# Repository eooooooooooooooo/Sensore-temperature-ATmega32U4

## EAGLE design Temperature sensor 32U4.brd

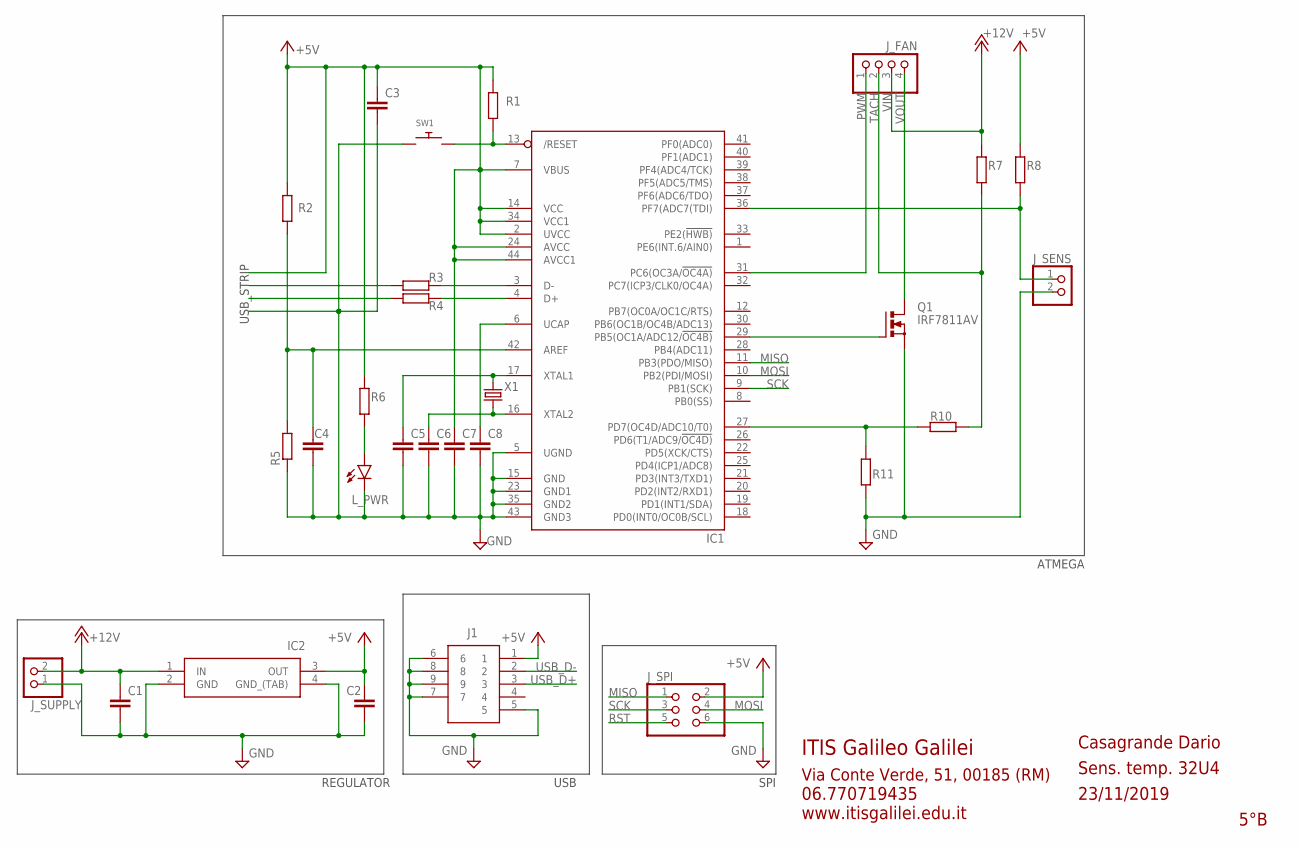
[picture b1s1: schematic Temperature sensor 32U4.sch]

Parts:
C1: 470n; C1206
C2: 47u; C1206
C3, C4, C8: 1u; C1206
C5, C6: 22p; C1206
C7: 100n; C1206
IC1: ATMEGA32U4-AU; TQFP44
IC2: LM2940CS-5.0_NOPB; TO254P1435X464-4N
J1: 10104111-0001LF; 101041110001LF
J_FAN: PINHD-1X4; 1X04
J_SENS: PINHD-1X2; 1X02
J_SPI: PINHD-2X3; 2X03
J_SUPPLY: PINHD-1X2; 1X02
L_PWR: LEDCHIPLED_1206; CHIPLED_1206
Q1: IRF7811AV; SO-08
R1, R7, R8, R10: 10k; R1206
R2: 1,8k; R1206
R3, R4: 10; R1206
R5: 8,2k; R1206
R6: 270; R1206
R11: 14k; R1206
SW1: SWITCH_PUSHBUTTONSOFTTOUCHSMD_SJ; PUSHBUTTON_SMD_SJ
X1: 16MHz; HC49/S

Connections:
+5V: C2.1, C3.1, C7.1, IC1.2 (UVCC), IC1.7 (VBUS), IC1.14 (VCC), IC1.24 (AVCC), IC1.34 (VCC1), IC1.44 (AVCC1), IC2.3 (OUT), J1.1, J_SPI.2, R1.2, R2.2, R6.1, R8.1
+12V: C1.1, IC2.1 (IN), J_SUPPLY.2
AREF: C4.1, IC1.42 (AREF), R2.1, R5.2
D+: IC1.4 (D+), R4.1
D-: IC1.3 (D-), R3.1
GND: C1.2, C2.2, C3.2, C4.2, C5.2, C6.2, C7.2, C8.2, IC1.5 (UGND), IC1.15 (GND), IC1.23 (GND1), IC1.35 (GND2), IC1.43 (GND3), IC2.2 (GND), IC2.4 (GND_(TAB)), J1.5, J1.6, J1.7, J1.8, J1.9, J_SENS.2, J_SPI.6, J_SUPPLY.1, L_PWR.C, Q1.1 (S), Q1.2 (S), Q1.3 (S), R5.1, R11.2, SW1.P$1
MISO: IC1.11 (PB3(PDO/MISO)), J_SPI.1
MOSI: IC1.10 (PB2(PDI/MOSI)), J_SPI.4
unnamed: L_PWR.A, R6.2
unnamed: IC1.29 (PB5(OC1A/ADC12/!OC4B)), Q1.4 (G)
PWM: IC1.31 (PC6(OC3A/!OC4A)), J_FAN.1
RST: IC1.13 (/RESET), J_SPI.5, R1.1, SW1.P$2
SCK: IC1.9 (PB1(SCK)), J_SPI.3
SENS: IC1.36 (PF7(ADC7(TDI)), J_SENS.1, R8.2
TACH: J_FAN.2, R7.2, R10.1
TACH_IN: IC1.27 (PD7(OC4D/ADC10/T0)), R10.2, R11.1
UCAP: C8.1, IC1.6 (UCAP)
USB_D+: J1.3, R4.2
USB_D-: J1.2, R3.2
VIN: J_FAN.3, R7.1
VOUT: J_FAN.4, Q1.5 (D), Q1.6 (D), Q1.7 (D), Q1.8 (D)
XTAL1: C5.1, IC1.17 (XTAL1), X1.2
XTAL2: C6.1, IC1.16 (XTAL2), X1.1

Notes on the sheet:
5°B
Casagrande Dario
Sens. temp. 32U4
23/11/2019
ITIS Galileo Galilei
Via Conte Verde, 51, 00185 (RM)
www.itisgalilei.edu.it
06.770719435
USB
SPI
REGULATOR
ATMEGA
USB_STRIP

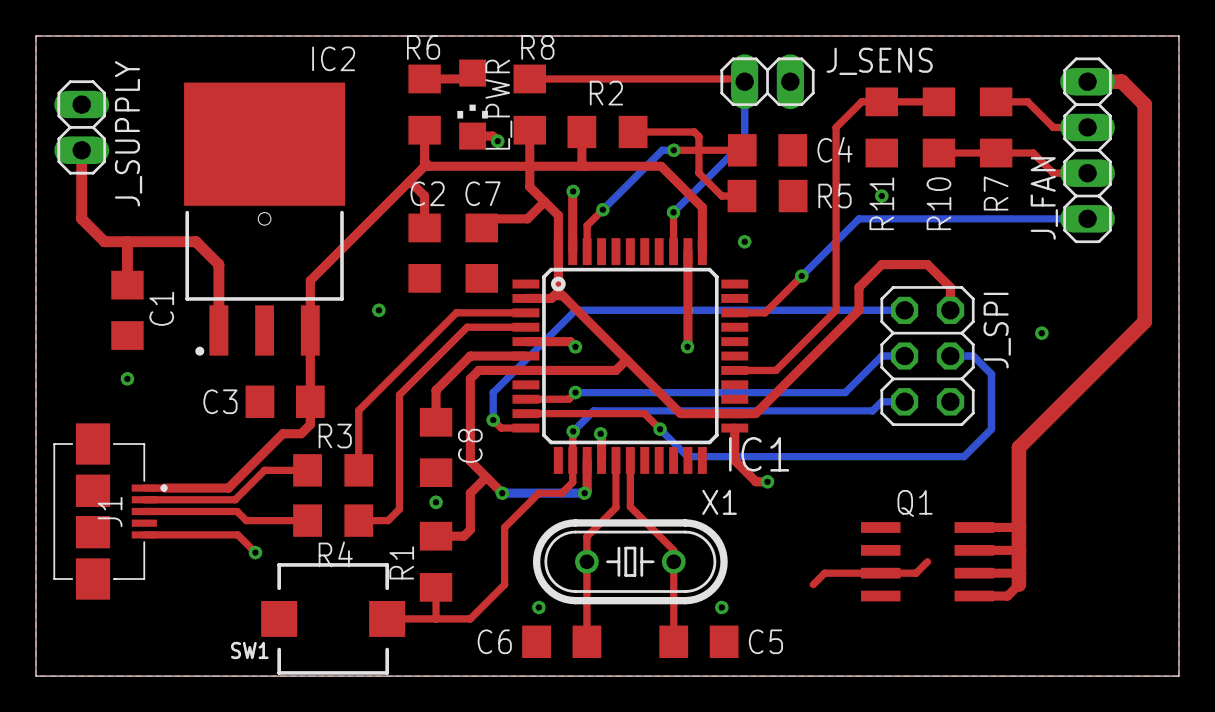
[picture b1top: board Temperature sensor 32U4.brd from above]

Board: 2 copper layers, 63.5 x 35.6 mm, 29 parts (0 on the bottom side), 23 nets.

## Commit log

2020-01-03 Removed backup files
2020-01-03 Create LICENSE
2020-01-03 Added BoM
2020-01-03 Fixed schematic and deleted backup files
2020-01-04 Fixed ground planes
2020-01-04 Deleted backup files
2020-01-09 Replaced BJT with a MOSFET
